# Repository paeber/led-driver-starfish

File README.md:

# LED Driver - Starfish
ESP32 based LED driver designed for use with ESPHome.

The pcb is designed with KiCad and has a ESP32-S3 with power and usb circuit. A total of four N-Channel FETs allow to switch 12V appliances (LED) upto 4.4A each. The four channels allow multiple LED strips or ones with RGBW etc.

## Features

- ESP32-S3 for use with ESPHome

- 4 Open-Drain Channels for RGBW
- 2 Buttons for user input
- WS2812 LED
- Multiple headers for further peripherals (I2C,  3V3, 5V, GPIOs)
- 6V to 15V Input

## ESPHome Code

YAML configuration for ESPHome. Adapt as you need for your setup. Code is relevant for latest version (rev B).

### Base

```yaml
substitutions:
  dev_name: Kitchen

esphome:
  name: kitchen-starfish
  friendly_name: kitchen-starfish
  comment: ESP32 based LED driver for 12 V LED Strips

  on_boot:
    light.turn_on:
      id: status_led
      brightness: 20%
      green: 30%
      
esp32:
  variant: esp32s3
  board: esp32-s3-devkitc-1
  framework:
    type: arduino
```

### Internal LED

```yaml
light:
  - platform: esp32_rmt_led_strip
    id: status_led
    rgb_order: GRB
    pin: GPIO38
    num_leds: 1
    rmt_channel: 0
    chipset: ws2812
    name: "Status"
    internal: true
```

### PWM Output

```yaml
output:
  - platform: ledc
    id: output_component1
    pin: GPIO6
    frequency: 19531

  - platform: ledc
    id: output_component2
    pin: GPIO5
    frequency: 19531
```

### Dimmable Light

```yaml
light:
  - platform: monochromatic
    name: ${dev_name} Ceiling
    output: output_component1
```

### Buttons

```yaml
binary_sensor:
  - platform: gpio
    pin: 
      number: GPIO8
      inverted: True
    name: ${dev_name} BTN_1

  - platform: gpio
    pin: 
      number: GPIO11
      inverted: True
    name: ${dev_name} BTN_2
```

### I2C Header

```yaml
i2c:
  scl: GPIO9
  sda: GPIO10
```

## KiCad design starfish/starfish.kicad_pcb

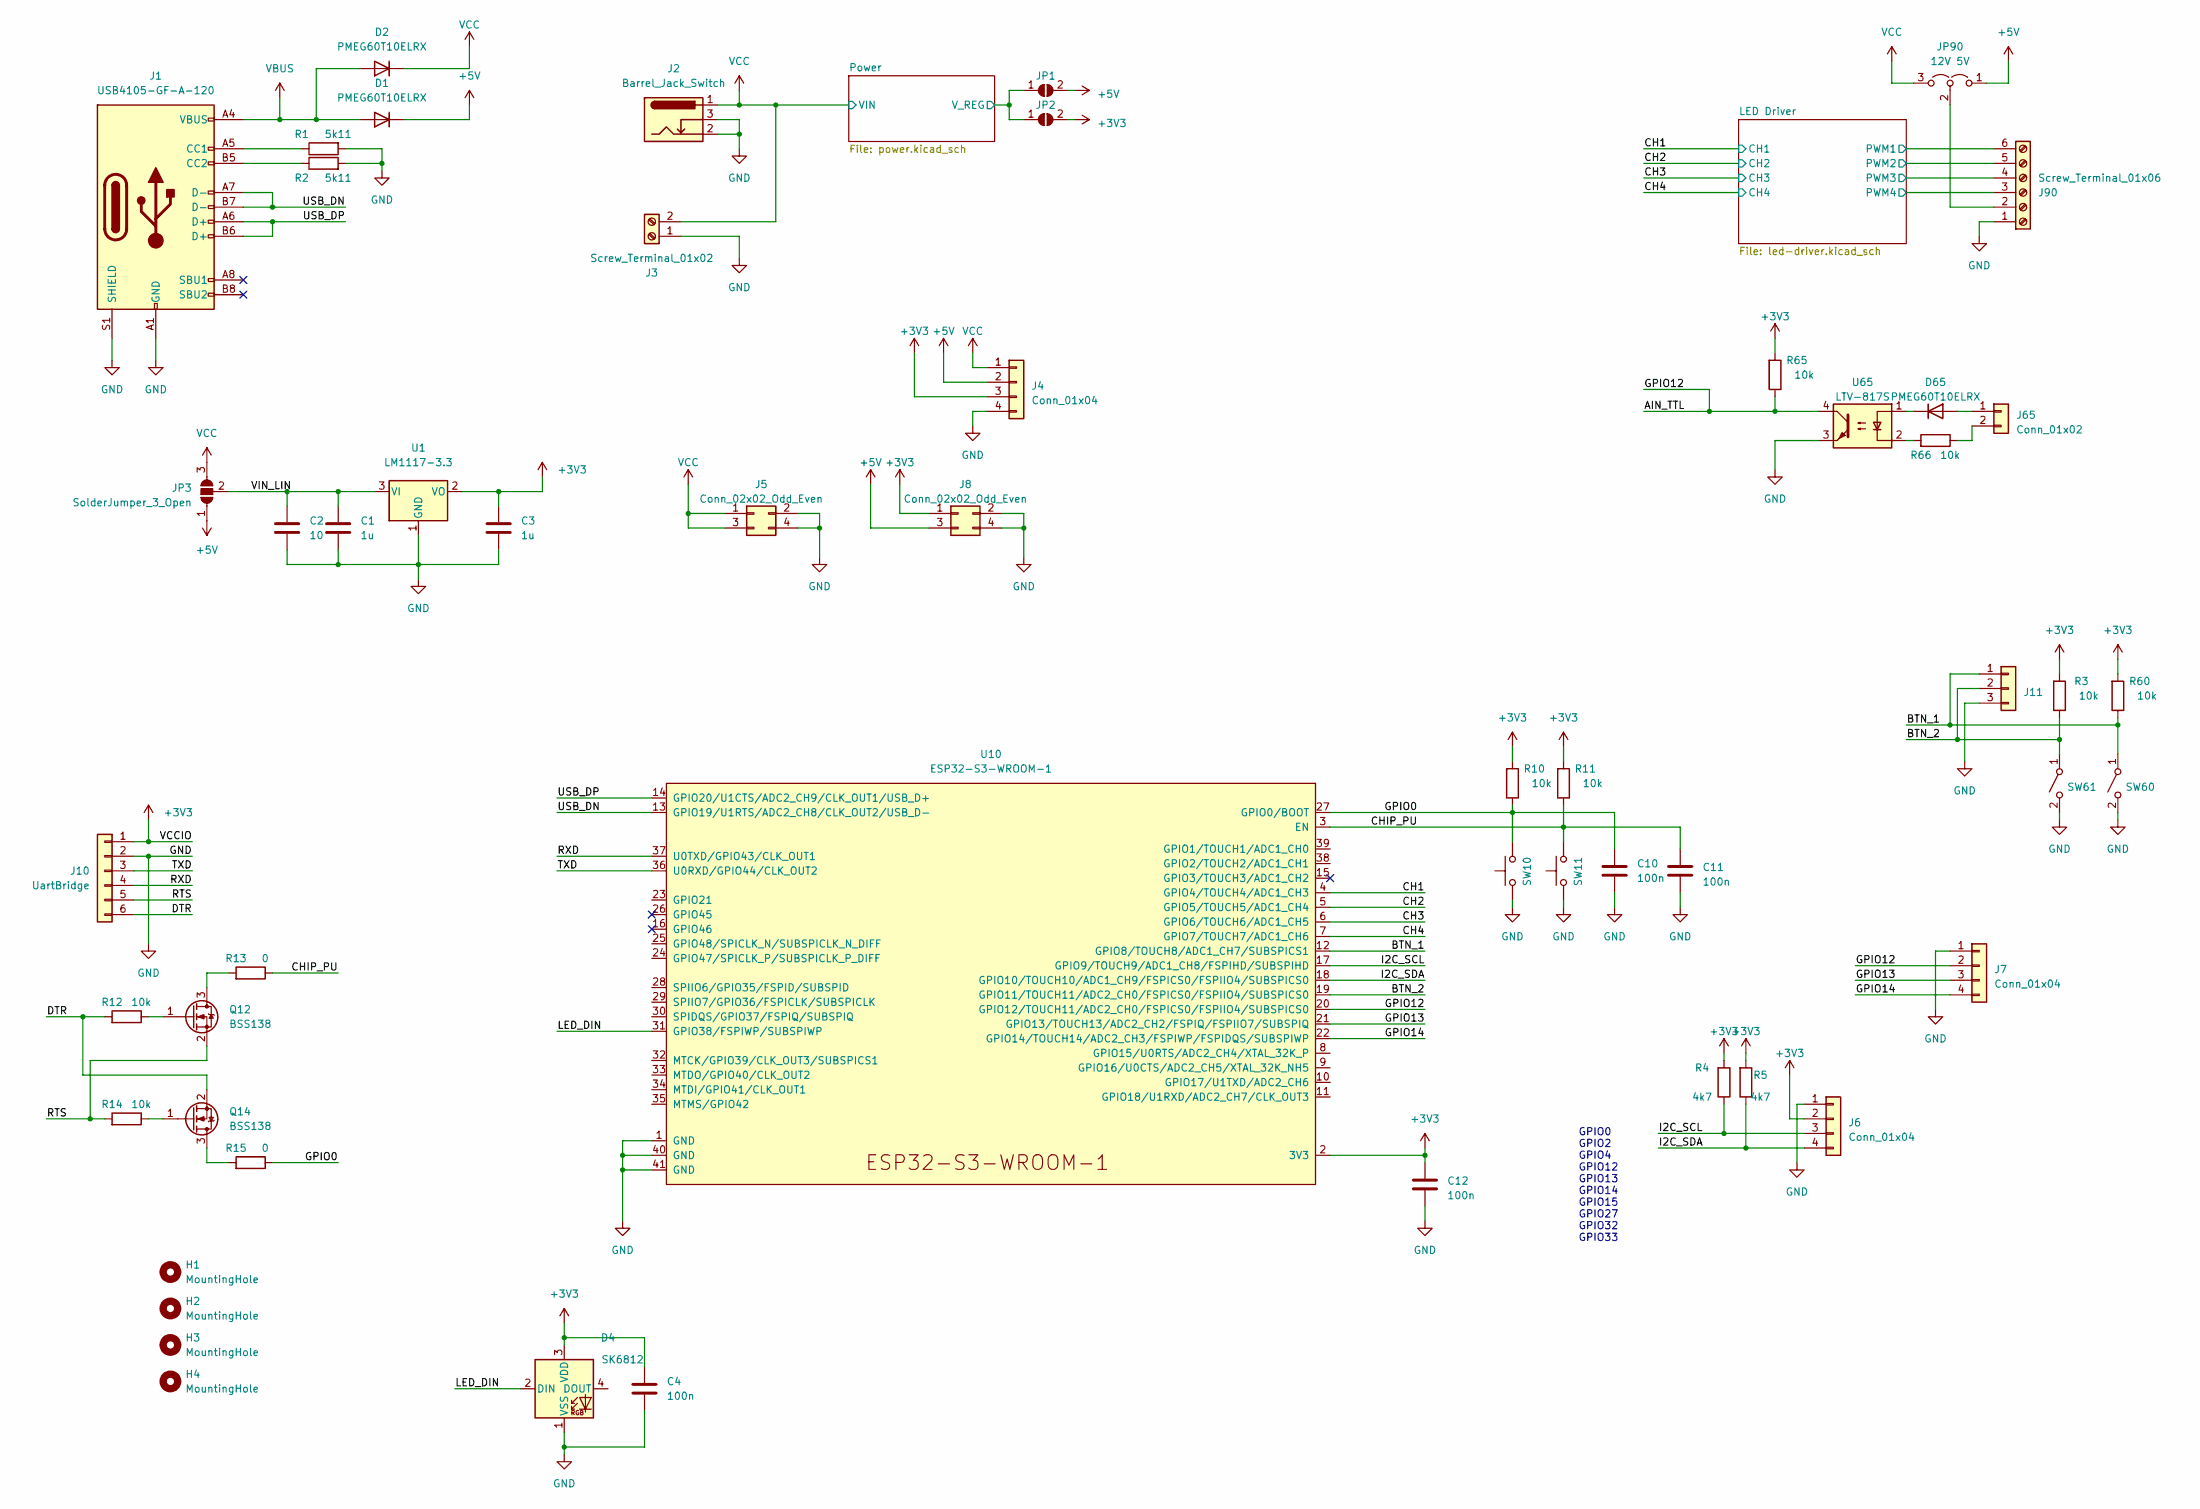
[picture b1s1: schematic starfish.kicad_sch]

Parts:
C1, C3: 1u; C_0805_2012Metric_Pad1.18x1.45mm_HandSolder
C2: 10; C_0805_2012Metric_Pad1.18x1.45mm_HandSolder
C4, C10, C11, C12: 100n; C_0603_1608Metric_Pad1.08x0.95mm_HandSolder; Mouser 581-06035C104KAT2A
D1, D2, D65: PMEG60T10ELRX; D_SOD-123; Mouser 771-PMEG60T10ELRX
D4: SK6812; LED_SK6812_PLCC4_5.0x5.0mm_P3.2mm
H1, H2, H3, H4: MountingHole; MountingHole_3.2mm_M3_DIN965_Pad_TopBottom
J1: USB4105-GF-A-120; USB_C_Receptacle_HRO_TYPE-C-31-M-12; Mouser 640-USB4105-GF-A-120
J2: Barrel_Jack_Switch; BarrelJack_Wuerth_6941xx301002; Mouser 992-CON-SOCJ-2155
J3: Screw_Terminal_01x02; CUI_TBP01R1-508-02BE; Mouser 490-TBP01R1-508-02BE
J4, J6, J7: Conn_01x04; PinSocket_1x04_P2.54mm_Vertical
J5, J8: Conn_02x02_Odd_Even; PinHeader_2x02_P2.54mm_Vertical
J10: UartBridge; PinSocket_1x06_P2.54mm_Vertical
J11: Conn_01x03; PinSocket_1x03_P2.54mm_Vertical
J65: Conn_01x02; PinHeader_1x02_P2.54mm_Vertical
J90: Screw_Terminal_01x06; CUI_TBP01R1-508-06BE; Mouser 490-TBP01R1-508-06BE
JP1, JP2: SolderJumper_2_Open; SolderJumper-2_P1.3mm_Open_RoundedPad1.0x1.5mm
JP3: SolderJumper_3_Open; SolderJumper-3_P1.3mm_Open_RoundedPad1.0x1.5mm
JP90: 12V 5V; SolderJumper-3_P1.3mm_Open_RoundedPad1.0x1.5mm_NumberLabels
Q12, Q14: BSS138; SOT-23
R1, R2: 5k11; R_0603_1608Metric_Pad0.98x0.95mm_HandSolder
R3, R10, R11, R12, R14, R60, R65, R66: 10k; R_0603_1608Metric_Pad0.98x0.95mm_HandSolder
R4, R5: 4k7; R_0603_1608Metric_Pad0.98x0.95mm_HandSolder
R13, R15: 0; R_0603_1608Metric_Pad0.98x0.95mm_HandSolder
SW10, SW11: PTS636SK25; SW_Tactile_SPST_NO_Straight_CK_PTS636Sx25SMTRLFS; Mouser 611-PTS636SK25SMTRLF
SW60, SW61: 1301.9315; 13019319; Mouser 693-1301.9315
U1: LM1117-3.3; SOT-223-3_TabPin2
U10: ESP32-S3-WROOM-1
U65: LTV-817S; SMDIP-4_W9.53mm

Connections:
+3V3: C3.1, C4.1, C12.1, D4.3 (VDD), J4.3, J6.2, J8.1, J10.1, JP2.2 (B), R3.2, R4.2, R5.2, R10.2, R11.2, R60.2, R65.2, U1.2 (VO), U10.2 (3V3)
+5V: D1.1 (K), J4.2, J8.3, JP1.2 (B), JP3.1 (A), JP90.1 (A)
/AIN_TTL: J7.2, R65.1, U10.20 (GPIO12/TOUCH11/ADC2_CH0/FSPICS0/FSPIIO4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), U65.4
/BTN_1: J11.1, R60.1, SW60.1 (A), U10.12 (GPIO8/TOUCH8/ADC1_CH7/SUBSPICS1)
/BTN_2: J11.2, R3.1, SW61.1 (A), U10.19 (GPIO11/TOUCH11/ADC2_CH0/FSPICS0/FSPIIO4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)
/CH1: U10.4 (GPIO4/TOUCH4/ADC1_CH3); also elsewhere on the board
/CH2: U10.5 (GPIO5/TOUCH5/ADC1_CH4); also elsewhere on the board
/CH3: U10.6 (GPIO6/TOUCH6/ADC1_CH5); also elsewhere on the board
/CH4: U10.7 (GPIO7/TOUCH7/ADC1_CH6); also elsewhere on the board
/CHIP_PU: C11.1, R11.1, R13.1, SW11.2, U10.3 (EN)
/DTR: J10.6, Q14.2 (S), R12.2
/GPIO0: C10.1, R10.1, R15.1, SW10.2, U10.27 (GPIO0/BOOT)
/GPIO13: J7.3, U10.21 (GPIO13/TOUCH13/ADC2_CH2/FSPIQ/FSPIIO7/S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)
/GPIO14: J7.4, U10.22 (GPIO14/TOUCH14/ADC2_CH3/FSPIWP/FSPIDQS/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)
/I2C_SCL: J6.3, R4.1, U10.17 (GPIO9/TOUCH9/ADC1_CH8/FSPIHD/SUBSPIHD)
/I2C_SDA: J6.4, R5.1, U10.18 (GPIO10/TOUCH10/ADC1_CH9/FSPICS0/FSPIIO4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)
/LED Driver/PWM1: J90.6; also elsewhere on the board
/LED Driver/PWM2: J90.5; also elsewhere on the board
/LED Driver/PWM3: J90.4; also elsewhere on the board
/LED Driver/PWM4: J90.3; also elsewhere on the board
/LED_DIN: D4.2 (DIN), U10.31 (GPIO38/FSPIWP/SUBSPIWP)
/Power/V_REG: JP1.1 (A), JP2.1 (A); also elsewhere on the board
/RTS: J10.5, Q12.2 (S), R14.2
/RXD: J10.4, U10.37 (U0TXD/GPIO43/CLK_OUT1)
/TXD: J10.3, U10.36 (U0RXD/GPIO44/CLK_OUT2)
/USB_DN: J1.A7 (D-), J1.B7 (D-), U10.13 (GPIO19/U1RTS/ADC2_CH8/CLK_OUT2/USB_D-)
/USB_DP: J1.A6 (D+), J1.B6 (D+), U10.14 (GPIO20/U1CTS/ADC2_CH9/CLK_OUT1/USB_D+)
/VIN_LIN: C1.1, C2.1, JP3.2 (C), U1.3 (VI)
GND: C1.2, C2.2, C3.2, C4.2, C10.2, C11.2, C12.2, D4.1 (VSS), J1.A1 (GND), J1.A12 (GND), J1.B1 (GND), J1.B12 (GND), J1.S1 (SHIELD), J2.2, J2.3, J3.1, J4.4, J5.2, J5.4, J6.1, J7.1, J8.2, J8.4, J10.2, J11.3, J90.1, R1.2, R2.2, SW10.1, SW11.1, SW60.2 (B), SW61.2 (B), U1.1 (GND), U10.1 (GND), U10.40 (GND), U10.41 (GND), U65.3; also elsewhere on the board
unnamed: D65.2 (A), J65.1
unnamed: D65.1 (K), U65.1
unnamed: J1.A5 (CC1), R1.1
unnamed: J1.B5 (CC2), R2.1
unnamed: J65.2, R66.1
unnamed: J90.2, JP90.2 (C)
unnamed: Q12.3 (D), R13.2
unnamed: Q12.1 (G), R12.1
unnamed: Q14.3 (D), R15.2
unnamed: Q14.1 (G), R14.1
unnamed: R66.2, U65.2
VBUS: D1.2 (A), D2.2 (A), J1.A4 (VBUS), J1.A9 (VBUS), J1.B4 (VBUS), J1.B9 (VBUS)
VCC: D2.1 (K), J2.1, J3.2, J4.1, J5.1, J5.3, JP3.3 (B), JP90.3 (B); also elsewhere on the board

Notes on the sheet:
GPIO0 GPIO2 GPIO4 GPIO12 GPIO13 GPIO14 GPIO15 GPIO27 GPIO32 GPIO33

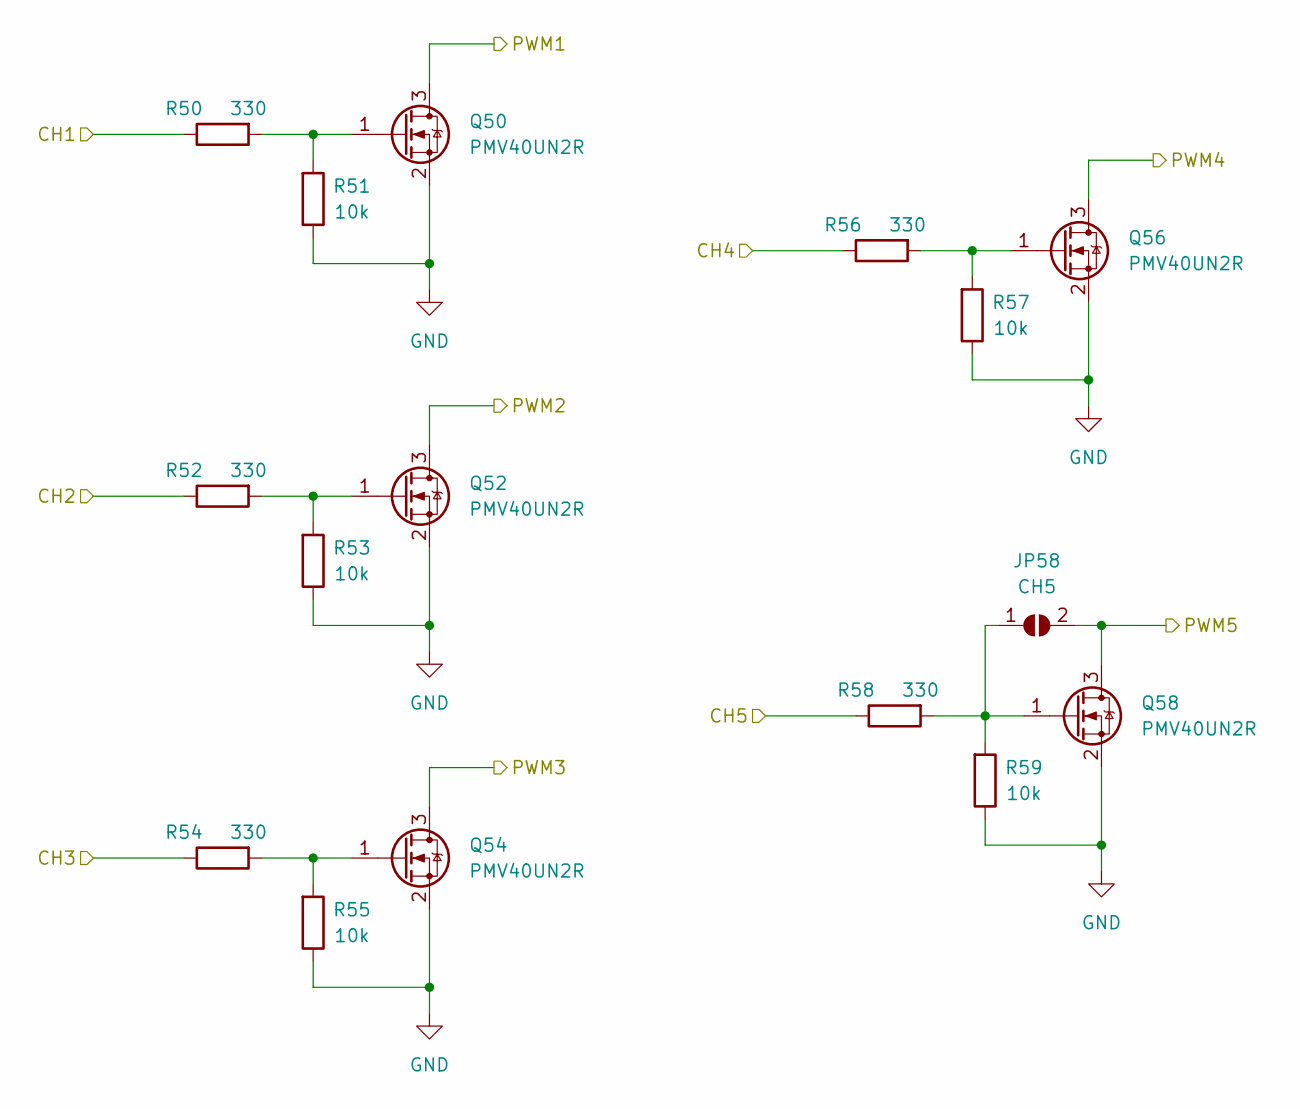
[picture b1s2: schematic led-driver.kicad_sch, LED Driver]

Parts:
JP58: CH5; SolderJumper-2_P1.3mm_Open_RoundedPad1.0x1.5mm
Q50, Q52, Q54, Q56: PMV40UN2R; SOT-23; LCSC C130869
Q58: PMV40UN2R; SOT-23; Mouser 771-PMV40UN2R
R50, R52, R54, R56, R58: 330; R_0603_1608Metric_Pad0.98x0.95mm_HandSolder
R51, R53, R55, R57, R59: 10k; R_0603_1608Metric_Pad0.98x0.95mm_HandSolder

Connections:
/CH1: R50.1; also elsewhere on the board
/CH2: R52.1; also elsewhere on the board
/CH3: R54.1; also elsewhere on the board
/CH4: R56.1; also elsewhere on the board
/LED Driver/PWM1: Q50.3 (D); also elsewhere on the board
/LED Driver/PWM2: Q52.3 (D); also elsewhere on the board
/LED Driver/PWM3: Q54.3 (D); also elsewhere on the board
/LED Driver/PWM4: Q56.3 (D); also elsewhere on the board
GND: Q50.2 (S), Q52.2 (S), Q54.2 (S), Q56.2 (S), Q58.2 (S), R51.1, R53.1, R55.1, R57.1, R59.1; also elsewhere on the board
unnamed: JP58.1 (A), Q58.1 (G), R58.2, R59.2
unnamed: JP58.2 (B), Q58.3 (D)
unnamed: Q50.1 (G), R50.2, R51.2
unnamed: Q52.1 (G), R52.2, R53.2
unnamed: Q54.1 (G), R54.2, R55.2
unnamed: Q56.1 (G), R56.2, R57.2

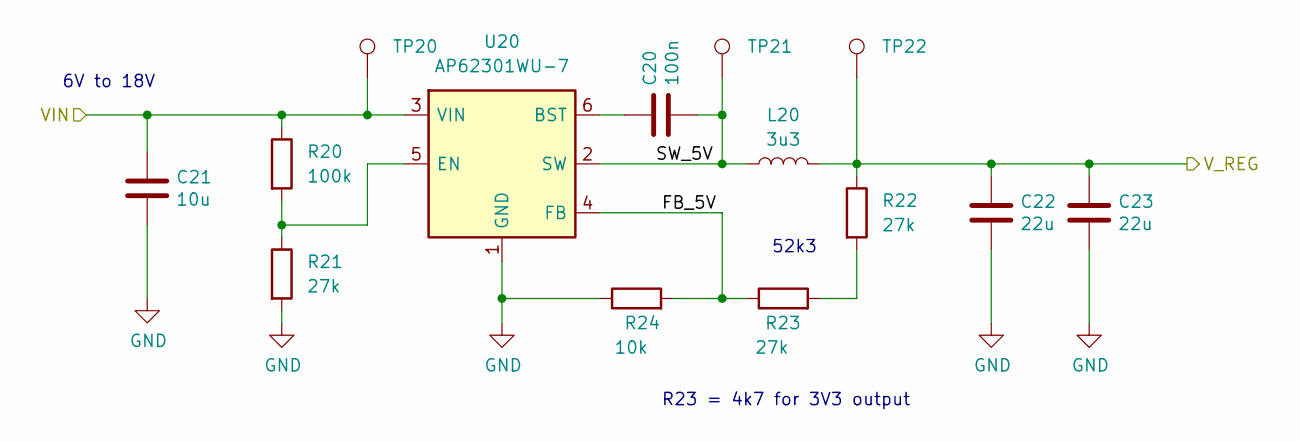
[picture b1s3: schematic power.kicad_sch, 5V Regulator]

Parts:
C20: 100n; C_0603_1608Metric_Pad1.08x0.95mm_HandSolder; Mouser 581-06035C104KAT2A
C21: 10u; C_1206_3216Metric; Mouser 581-1206DD106MAT2A
C22, C23: 22u; C_1206_3216Metric; Mouser 581-1206YD226MAT2A
L20: 3u3; XAL6030182MEB-HandSolder; Manufacturer_Part_Number XAL6030-332MEC; Mouser 994-XAL6030-332MEC
R20: 100k; R_0603_1608Metric_Pad0.98x0.95mm_HandSolder
R21, R22, R23: 27k; R_0603_1608Metric_Pad0.98x0.95mm_HandSolder
R24: 10k; R_0603_1608Metric_Pad0.98x0.95mm_HandSolder
TP20, TP21, TP22: TestPoint; TestPoint_Pad_D1.5mm
U20: AP62301WU-7; TSOT-26; Manufacturer_Part_Number AP62301WU-7; Mouser 621-AP62301WU-7

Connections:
/Power/FB_5V: R23.1, R24.2, U20.4 (FB)
/Power/SW_5V: C20.2, L20.1, TP21.1, U20.2 (SW)
/Power/V_REG: C22.1, C23.1, L20.2, R22.1, TP22.1; also elsewhere on the board
GND: C21.2, C22.2, C23.2, R21.2, R24.1, U20.1 (GND); also elsewhere on the board
unnamed: R22.2, R23.2
unnamed: C20.1, U20.6 (BST)
unnamed: R20.2, R21.1, U20.5 (EN)
VCC: C21.1, R20.1, TP20.1, U20.3 (VIN); also elsewhere on the board

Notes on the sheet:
52k3
R23 = 4k7 for 3V3 output
6V to 18V

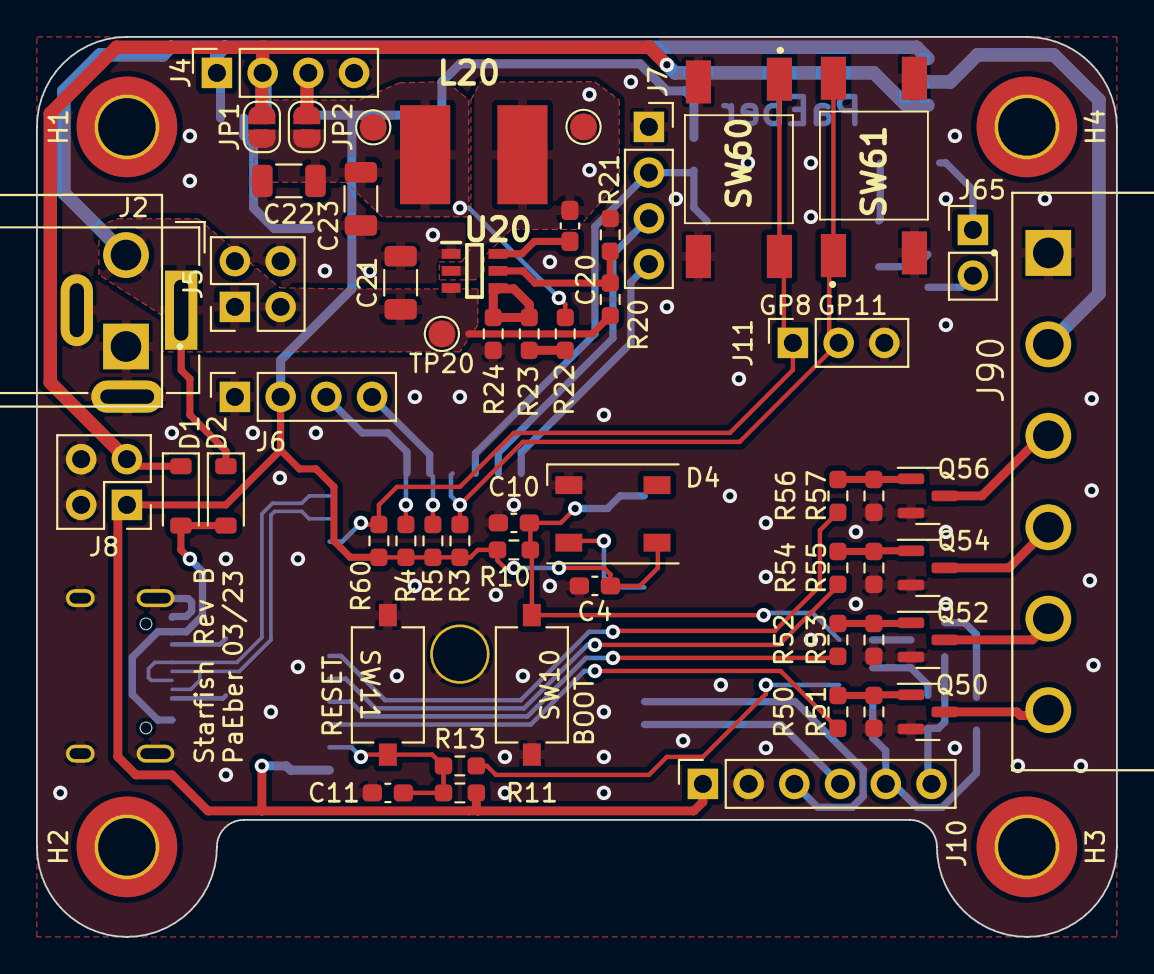
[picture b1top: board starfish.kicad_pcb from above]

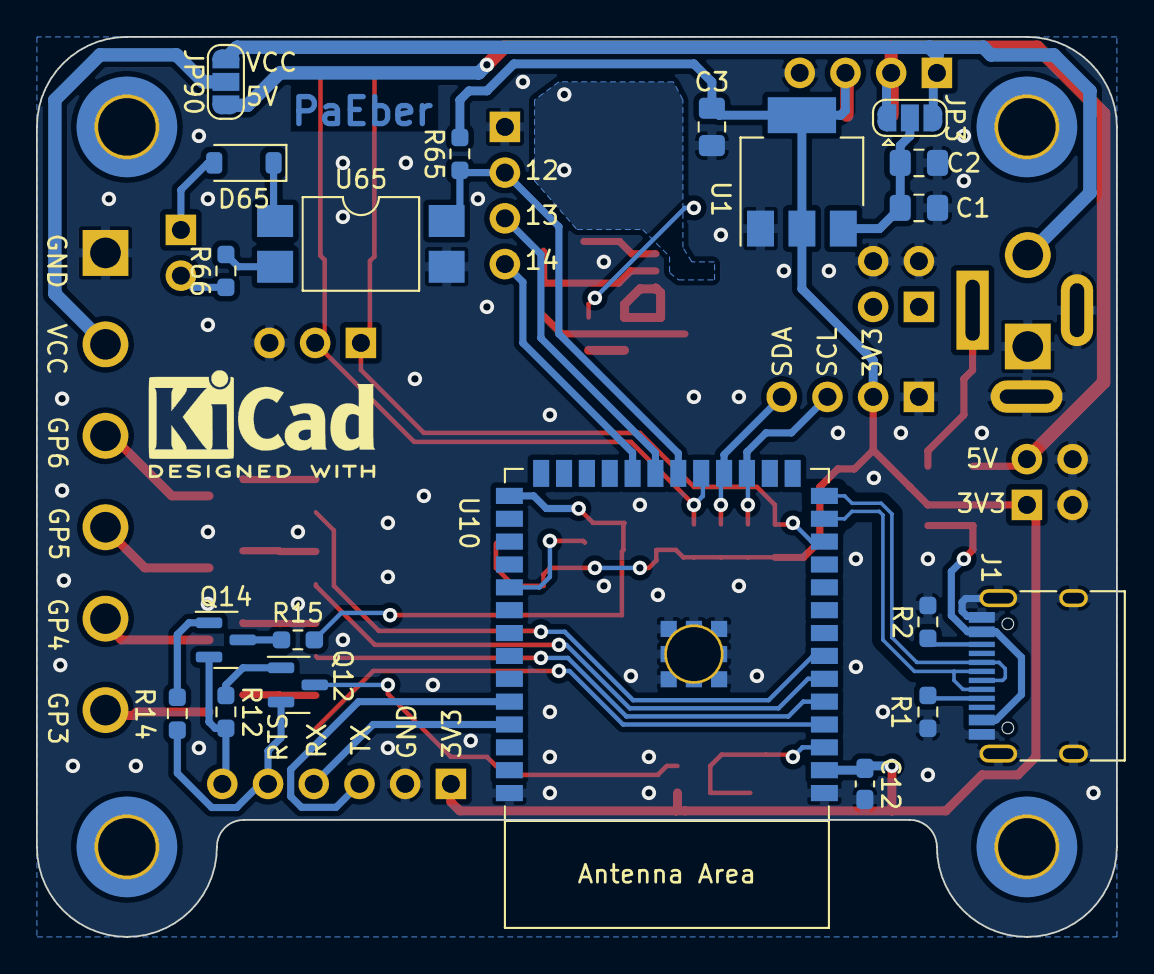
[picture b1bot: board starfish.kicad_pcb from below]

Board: 2 copper layers, 60.0 x 50.0 mm, 80 parts (20 on the bottom side), 51 nets.

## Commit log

2023-02-17 Add hardware design to github
2023-03-06 Start rev b
2023-03-07 Add some components
2023-03-08 Power progress
2023-03-09 Rev b progress
2023-03-11 Layout progress
2023-03-13 RevB first gerber export
2023-06-15 rev B pcb complete
2024-06-19 Update mechanical
